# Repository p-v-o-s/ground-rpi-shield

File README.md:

ground-rpi-shield
=================

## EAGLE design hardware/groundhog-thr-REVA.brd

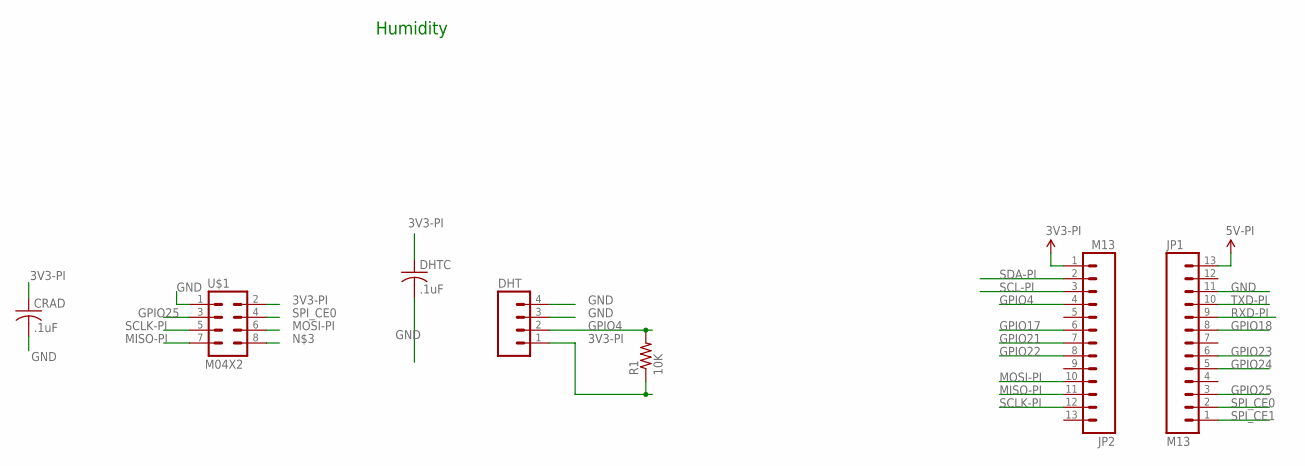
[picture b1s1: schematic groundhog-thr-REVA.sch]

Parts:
CRAD: .1uF; C0805
DHT: M04PTH; 1X04
DHTC: .1uF; C0805
JP1, JP2: M13; 1X13
R1: 10K; R0805
U$1: M04X2; 2X4

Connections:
3V3-PI: CRAD.1, DHT.1, DHTC.1, JP2.1, R1.1, U$1.2
5V-PI: JP1.13
GND: CRAD.2, DHT.3, DHT.4, DHTC.2, JP1.11, U$1.1
GPIO4: DHT.2, JP2.4, R1.2
GPIO17: JP2.6
GPIO18: JP1.8
GPIO21: JP2.7
GPIO22: JP2.8
GPIO23: JP1.6
GPIO24: JP1.5
GPIO25: JP1.3, U$1.3
MISO-PI: JP2.11, U$1.7
MOSI-PI: JP2.10, U$1.6
RXD-PI: JP1.9
SCL-PI: JP2.3
SCLK-PI: JP2.12, U$1.5
SDA-PI: JP2.2
SPI_CE0: JP1.2, U$1.4
SPI_CE1: JP1.1
TXD-PI: JP1.10

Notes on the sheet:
Humidity

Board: 2 copper layers, 7 parts (0 on the bottom side), 8 nets, no tracks yet.

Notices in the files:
parts and their libraries:
SparkFun-Connectors: Licensing: Creative Commons ShareAlike 4.0 International - https://creativecommons.org/licenses/by-sa/4.0
